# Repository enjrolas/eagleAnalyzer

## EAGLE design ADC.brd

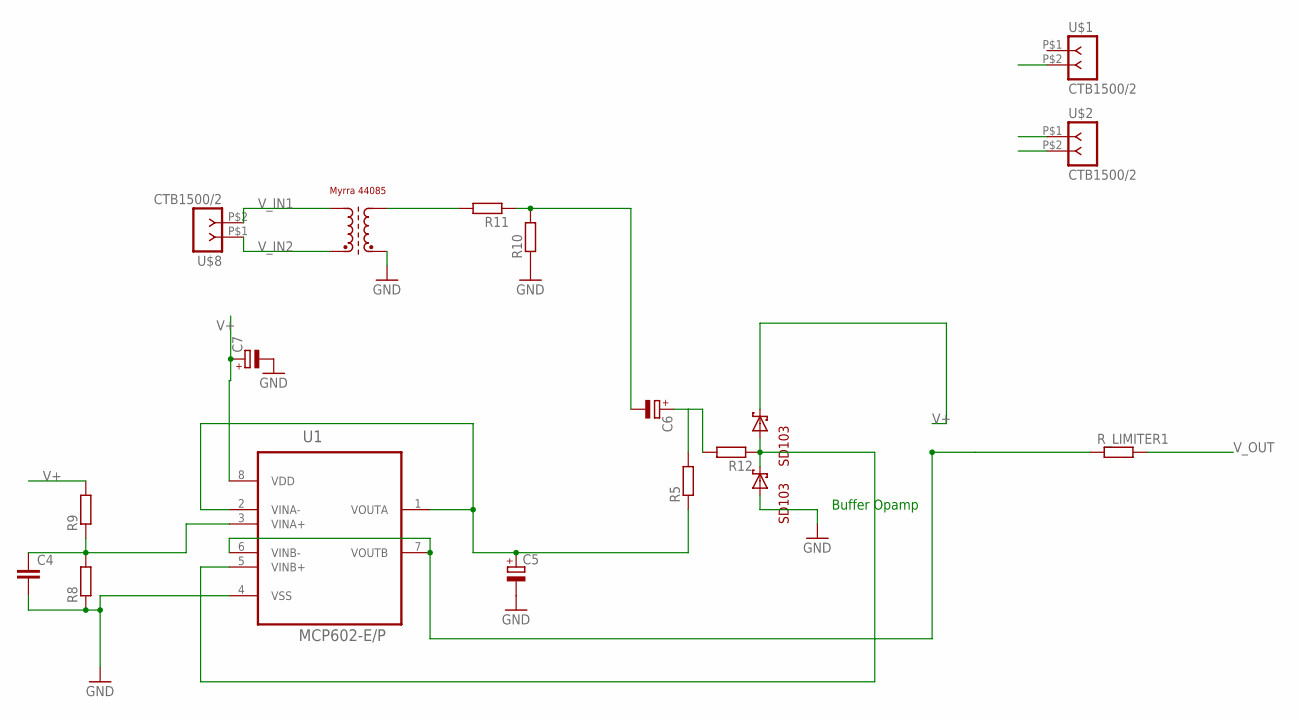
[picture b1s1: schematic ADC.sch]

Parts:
C4: C5P; C050-030-075
C5, C6, C7: CPOL1; E2,5-7---100UF
R5, R8, R9, R10, R11, R12: R; 0207/10
R_LIMITER1: R; 0207/10
U1: MCP602-E/P; DIP254P762X508-8P
U$1, U$2, U$8: CTB1500/2; CTB1500-2
U$5: MYRRA_4408; 4408
U$6, U$7: SD103A; D035-10

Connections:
GND: C4.2, C5.-, C7.-, R8.1, R10.1, U1.4 (VSS), U$2.P$1 (1), U$5.PIN9 (E2), U$7.A
unnamed: R_LIMITER1.1, U1.6 (VINB-), U1.7 (VOUTB)
unnamed: C5.+, R5.1, U1.1 (VOUTA), U1.2 (VINA-)
unnamed: C4.1, R8.2, R9.1, U1.3 (VINA+)
unnamed: R12.1, U1.5 (VINB+), U$6.A, U$7.C
unnamed: C6.-, R10.2, R11.1
unnamed: R11.2, U$5.PIN7 (A2)
unnamed: C6.+, R5.2, R12.2
V+: C7.+, R9.2, U1.8 (VDD), U$1.P$2 (2), U$6.C
V_IN1: U$5.PIN5 (A1), U$8.P$2 (2)
V_IN2: U$5.PIN1 (E1), U$8.P$1 (1)
V_OUT: R_LIMITER1.2, U$2.P$2 (2)

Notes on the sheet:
Buffer Opamp

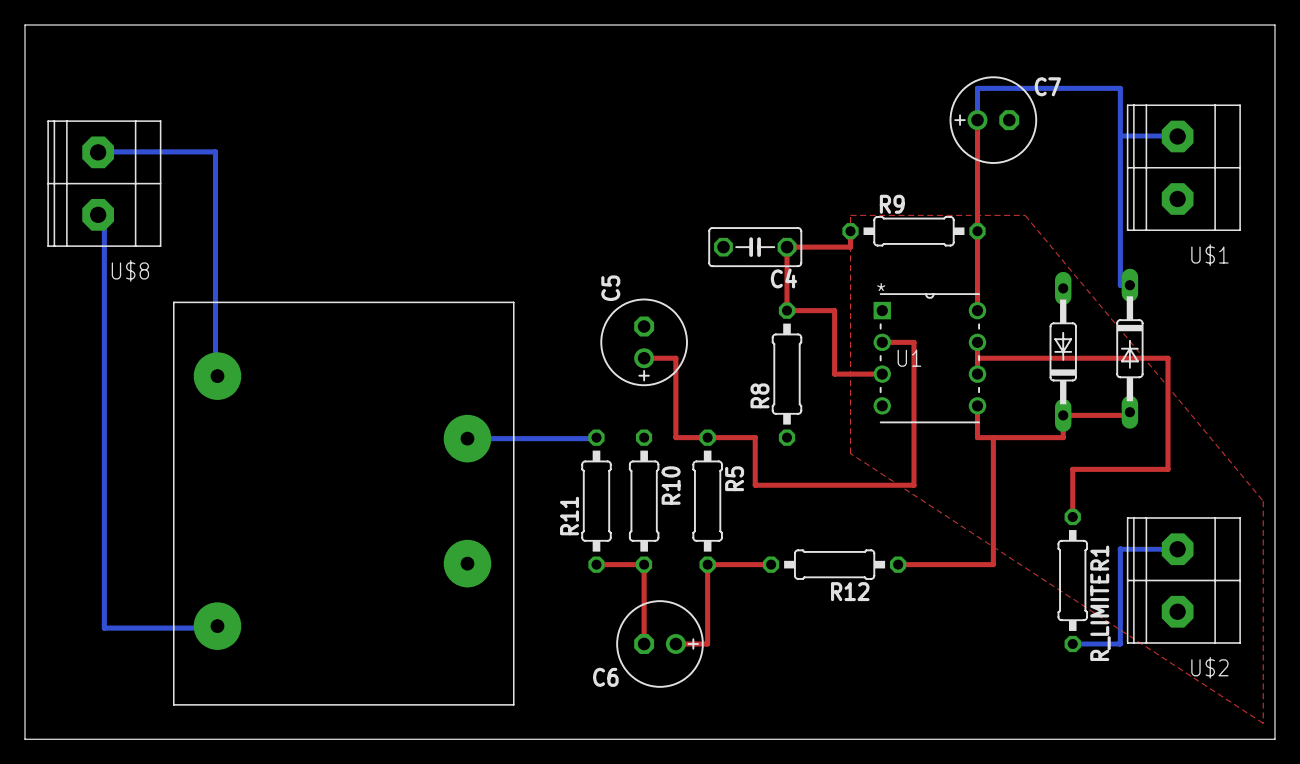
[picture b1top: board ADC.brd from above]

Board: 2 copper layers, 100.0 x 57.1 mm, 18 parts (0 on the bottom side), 12 nets.

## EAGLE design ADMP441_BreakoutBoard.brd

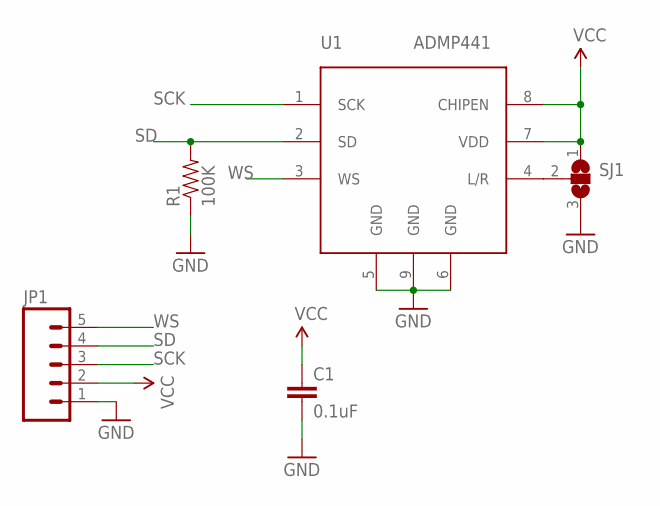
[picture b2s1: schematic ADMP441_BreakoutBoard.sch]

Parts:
C1: 0.1uF; 0603-CAP
JP1: M05PTH; 1X05
R1: 100K; 0603-RES
SJ1: SJ2W; SJ_2
U1: ADMP441

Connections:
GND: C1.2, JP1.1, R1.1, SJ1.3, U1.5 (GND), U1.6 (GND), U1.9 (GND)
unnamed: SJ1.2, U1.4 (L/R)
SCK: JP1.3, U1.1 (SCK)
SD: JP1.4, R1.2, U1.2 (SD)
VCC: C1.1, JP1.2, SJ1.1, U1.7 (VDD), U1.8 (CHIPEN)
WS: JP1.5, U1.3 (WS)

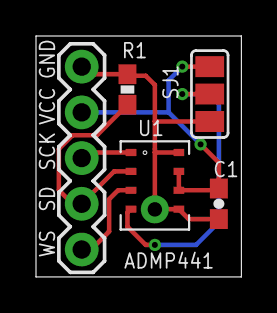
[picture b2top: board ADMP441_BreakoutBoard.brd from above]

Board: 2 copper layers, 11.4 x 13.4 mm, 5 parts (0 on the bottom side), 6 nets.

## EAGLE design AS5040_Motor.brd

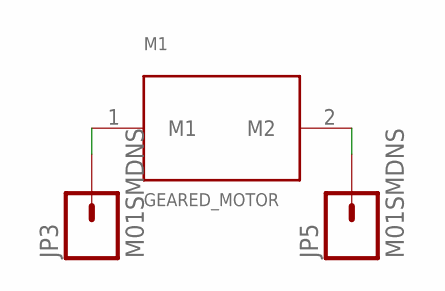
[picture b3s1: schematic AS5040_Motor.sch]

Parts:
JP3, JP5: M01SMDNS; 1X01NS
M1: GEARED_MOTOR

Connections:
unnamed: JP5.1, M1.2 (M2)
unnamed: JP3.1, M1.1 (M1)

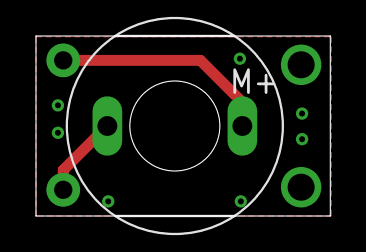
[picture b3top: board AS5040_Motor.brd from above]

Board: 2 copper layers, 16.4 x 10.0 mm, 3 parts (0 on the bottom side), 2 nets.

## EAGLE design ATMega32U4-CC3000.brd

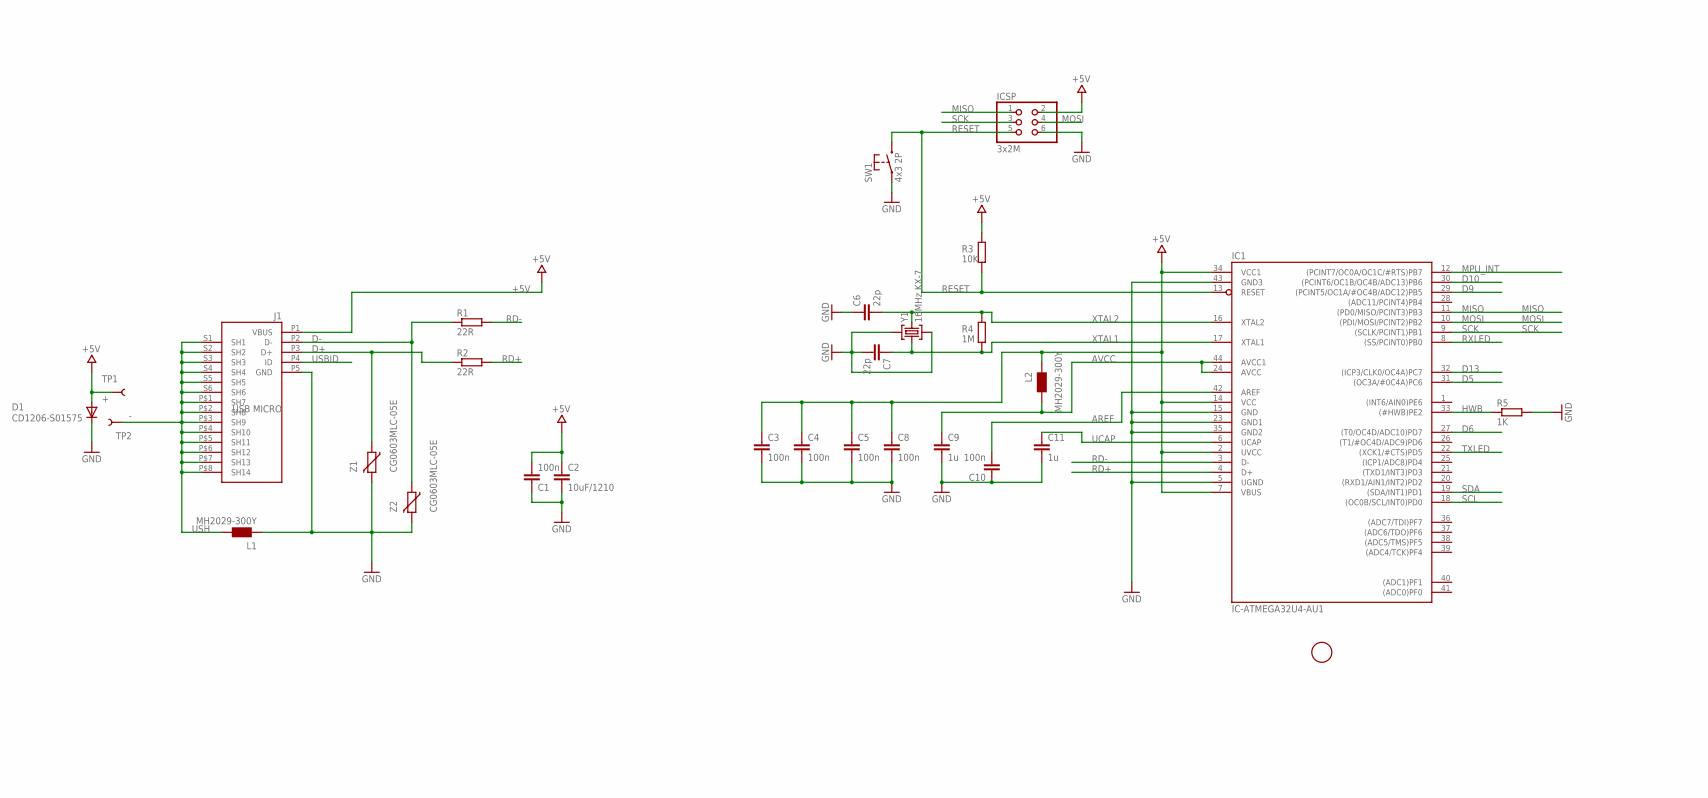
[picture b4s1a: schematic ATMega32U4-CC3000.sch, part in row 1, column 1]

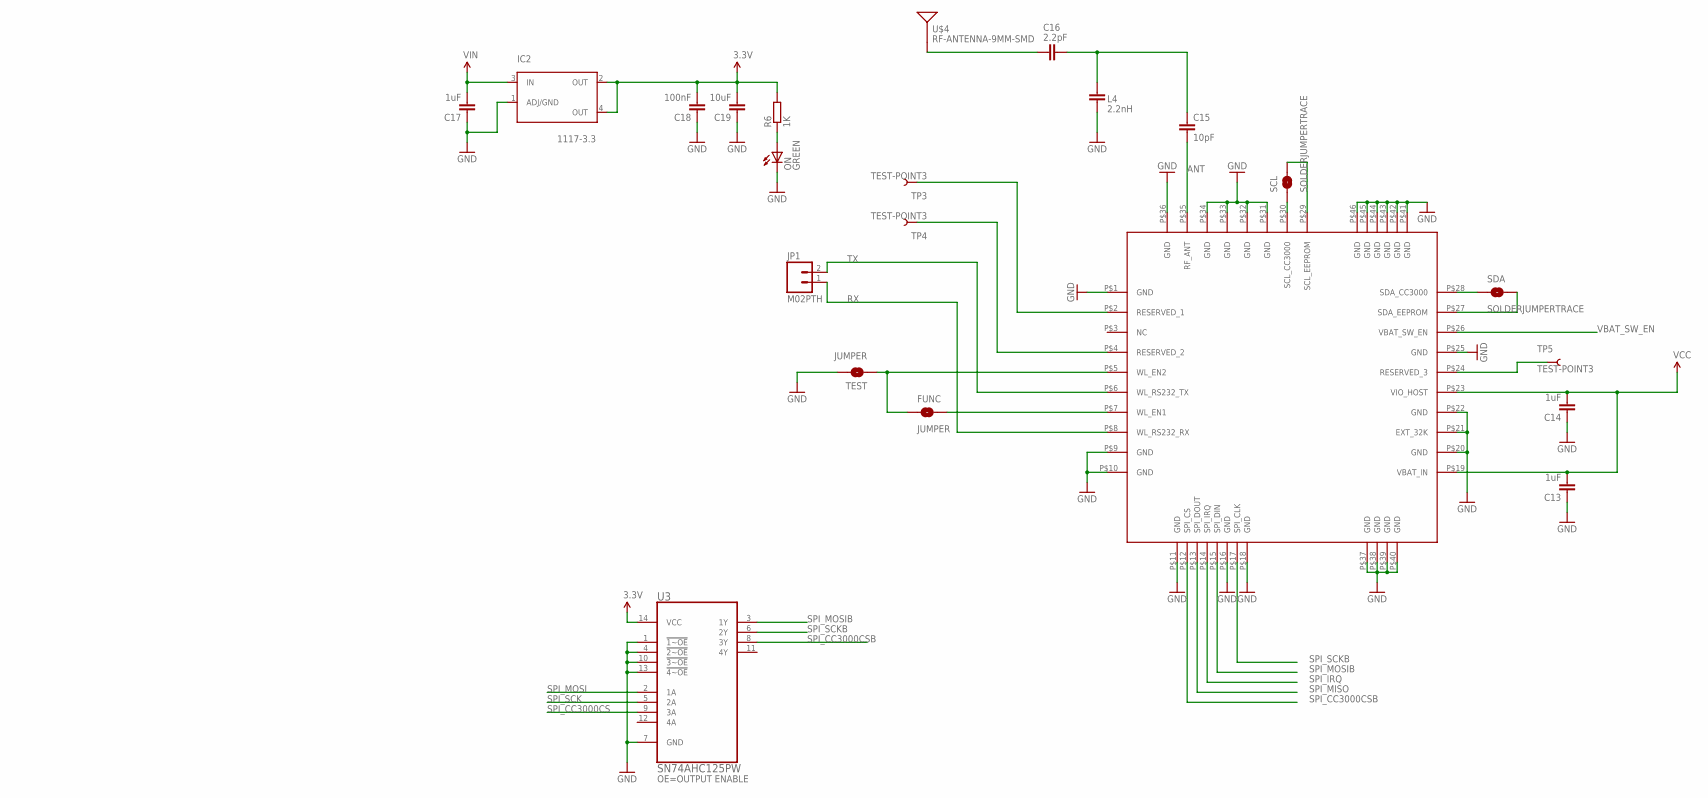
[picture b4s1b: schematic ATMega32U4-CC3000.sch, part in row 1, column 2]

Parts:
C1: 100n; C0603-ROUND
C2: 10uF/1210; CAP-1210_SMC-B-SMT
C3, C4, C5, C8, C10: 100n; CAP-0402-SMT-ROUND
C6, C7: 22p; CAP-0402-SMT-ROUND
C9, C11: 1u; CAP-0402-SMT-ROUND
C13, C14, C17: 1uF; CAP-0603-SMT-ROUND
C15: 10pF; CAP-0603-SMT-ROUND
C16: 2.2pF; CAP-0603-SMT-ROUND
C18: 100nF; CAP-0603-SMT-ROUND
C19: 10uF; CAP-1210_SMC-B-SMT
D1: CD1206-S01575; DIODE-1206-SMT
FID1: FIDUCIALMOUNT; FIDUCIA-MOUNT
FUNC: JUMPER; SJ_2S-TRACE
IC1: IC-ATMEGA32U4-AU1; QFP-10X10-44P
IC2: 1117-3.3; LDO-SOT223
ICSP: 3x2M; 2X03
J1: USB MICRO; CON2_USB_MICRO_B_AT
JP1: M02PTH; 1X02
L1, L2: MH2029-300Y; 0805
L4: 2.2nH; CAP-0603-SMT-ROUND
ON: GREEN; LED-0805-SMT
R1, R2: 22R; RESISTOR-0402-SMT-ROUND
R3: 10K; RESISTOR-0402-SMT-ROUND
R4: 1M; RESISTOR-0402-SMT-ROUND
R5: 1K; RESISTOR-0402-SMT-ROUND
R6: 1K; RESISTOR-0603-SMT-ROUND
SCL: SOLDERJUMPERTRACE; SJ_2S-TRACE
SDA: SOLDERJUMPERTRACE; SJ_2S-TRACE
SW1: 4x3 2P; SWITCH-2.1-SMT
TEST: JUMPER; SJ_2S-NO
TP1: +; PAD.03X.05
TP2: -; PAD.03X.05
TP3, TP4, TP5: TEST-POINT3; PAD.03X.03
U1: CC3000
U3: SN74AHC125PW; SOP65P640X120-14N
U$4: RF-ANTENNA-9MM-SMD; RF-ANTENNA-9MM
Y1: 16MHz KX-7; CRYSTAL-3.2-2.5
Z1, Z2: CG0603MLC-05E; CT/CN0603

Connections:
3.3V: C13.2, C14.2, C18.2, C19.- (2), IC2.2 (OUT), IC2.4 (OUT), R6.2, U1.P$19 (VBAT_IN), U1.P$23 (VIO_HOST), U3.14 (VCC)
+5V: C1.2, C2.+ (1), C3.1, C4.1, C5.1, C8.1, D1.A, IC1.2 (UVCC), IC1.7 (VBUS), IC1.14 (VCC), IC1.34 (VCC1), ICSP.2, J1.P1 (VBUS), L2.1, R3.1, TP1.P$1
ANT: C15.2, U1.P$35 (RF_ANT)
AREF: C10.2, IC1.42 (AREF)
AVCC: C9.1, IC1.24 (AVCC), IC1.44 (AVCC1), L2.2
D5: IC1.31 ((OC3A/#0C4A)PC6)
D6: IC1.27 ((T0/OC4D/ADC10)PD7)
D9: IC1.29 ((PCINT5/OC1A/#OC4B/ADC12)PB5)
D10: IC1.30 ((PCINT6/OC1B/OC4B/ADC13)PB6)
D13: IC1.32 ((ICP3/CLK0/OC4A)PC7)
D+: J1.P3 (D+), R2.1, Z1.1
D-: J1.P2 (D-), R1.1, Z2.1
GND: C1.1, C2.- (2), C3.2, C4.2, C5.2, C6.1, C7.2, C8.2, C9.2, C10.1, C11.2, C13.1, C14.1, C17.1, C18.1, C19.+ (1), D1.C, IC1.5 (UGND), IC1.15 (GND), IC1.23 (GND1), IC1.35 (GND2), IC1.43 (GND3), IC2.1 (ADJ/GND), ICSP.6, J1.P5 (GND), L1.1, L4.1, ON.C, R5.2, SW1.1, TEST.2, U1.P$1 (GND), U1.P$9 (GND), U1.P$10 (GND), U1.P$11 (GND), U1.P$16 (GND), U1.P$18 (GND), U1.P$20 (GND), U1.P$21 (EXT_32K), U1.P$22 (GND), U1.P$25 (GND), U1.P$31 (GND), U1.P$32 (GND), U1.P$33 (GND), U1.P$34 (GND), U1.P$36 (GND), U1.P$37 (GND), U1.P$38 (GND), U1.P$39 (GND), U1.P$40 (GND), U1.P$41 (GND), U1.P$42 (GND), U1.P$43 (GND), U1.P$44 (GND), U1.P$45 (GND), U1.P$46 (GND), U3.1 (!1~OE), U3.4 (!2~OE), U3.7 (GND), U3.10 (!3~OE), U3.13 (!4~OE), Y1.2 (GND), Y1.4 (GND), Z1.2, Z2.2
HWB: IC1.33 ((#HWB)PE2), R5.1
MISO: IC1.11 ((PD0/MISO/PCINT3)PB3), ICSP.1
MOSI: IC1.10 ((PDI/MOSI/PCINT2)PB2), ICSP.4
MPU_INT: IC1.12 ((PCINT7/OC0A/OC1C/#RTS)PB7)
unnamed: FUNC.2, U1.P$7 (WL_EN1)
unnamed: FUNC.1, TEST.1, U1.P$5 (WL_EN2)
unnamed: TP3.P$1, U1.P$2 (RESERVED_1)
unnamed: TP4.P$1, U1.P$4 (RESERVED_2)
unnamed: TP5.P$1, U1.P$24 (RESERVED_3)
unnamed: ON.A, R6.1
unnamed: C15.1, C16.2, L4.2
unnamed: SCL.1, U1.P$30 (SCL_CC3000)
unnamed: C16.1, U$4.SIG
unnamed: SCL.2, U1.P$29 (SCL_EEPROM)
unnamed: SDA.1, U1.P$28 (SDA_CC3000)
unnamed: SDA.2, U1.P$27 (SDA_EEPROM)
RD+: IC1.4 (D+), R2.2
RD-: IC1.3 (D-), R1.2
RESET: IC1.13 (RESET), ICSP.5, R3.2, SW1.2
RX: JP1.1, U1.P$8 (WL_RS232_RX)
RXLED: IC1.8 ((SS/PCINT0)PB0)
SCK: IC1.9 ((SCLK/PCINT1)PB1), ICSP.3
SCL: IC1.18 ((OC0B/SCL/INT0)PD0)
SDA: IC1.19 ((SDA/INT1)PD1)
SPI_CC3000CS: U3.9 (3A)
SPI_CC3000CSB: U1.P$12 (SPI_CS), U3.8 (3Y)
SPI_IRQ: U1.P$14 (SPI_IRQ)
SPI_MISO: U1.P$13 (SPI_DOUT)
SPI_MOSI: U3.2 (1A)
SPI_MOSIB: U1.P$15 (SPI_DIN), U3.3 (1Y)
SPI_SCK: U3.5 (2A)
SPI_SCKB: U1.P$17 (SPI_CLK), U3.6 (2Y)
TX: JP1.2, U1.P$6 (WL_RS232_TX)
TXLED: IC1.22 ((XCK1/#CTS)PD5)
UCAP: C11.1, IC1.6 (UCAP)
USBID: J1.P4 (ID)
USH: J1.P$1 (SH7), J1.P$2 (SH8), J1.P$3 (SH9), J1.P$4 (SH10), J1.P$5 (SH11), J1.P$6 (SH12), J1.P$7 (SH13), J1.P$8 (SH14), J1.S1 (SH1), J1.S2 (SH2), J1.S3 (SH3), J1.S4 (SH4), J1.S5 (SH5), J1.S6 (SH6), L1.2, TP2.P$1
VBAT_SW_EN: U1.P$26 (VBAT_SW_EN)
VIN: C17.2, IC2.3 (IN)
XTAL1: C7.1, IC1.17 (XTAL1), R4.1, Y1.1 (C1)
XTAL2: C6.2, IC1.16 (XTAL2), R4.2, Y1.3 (C2)

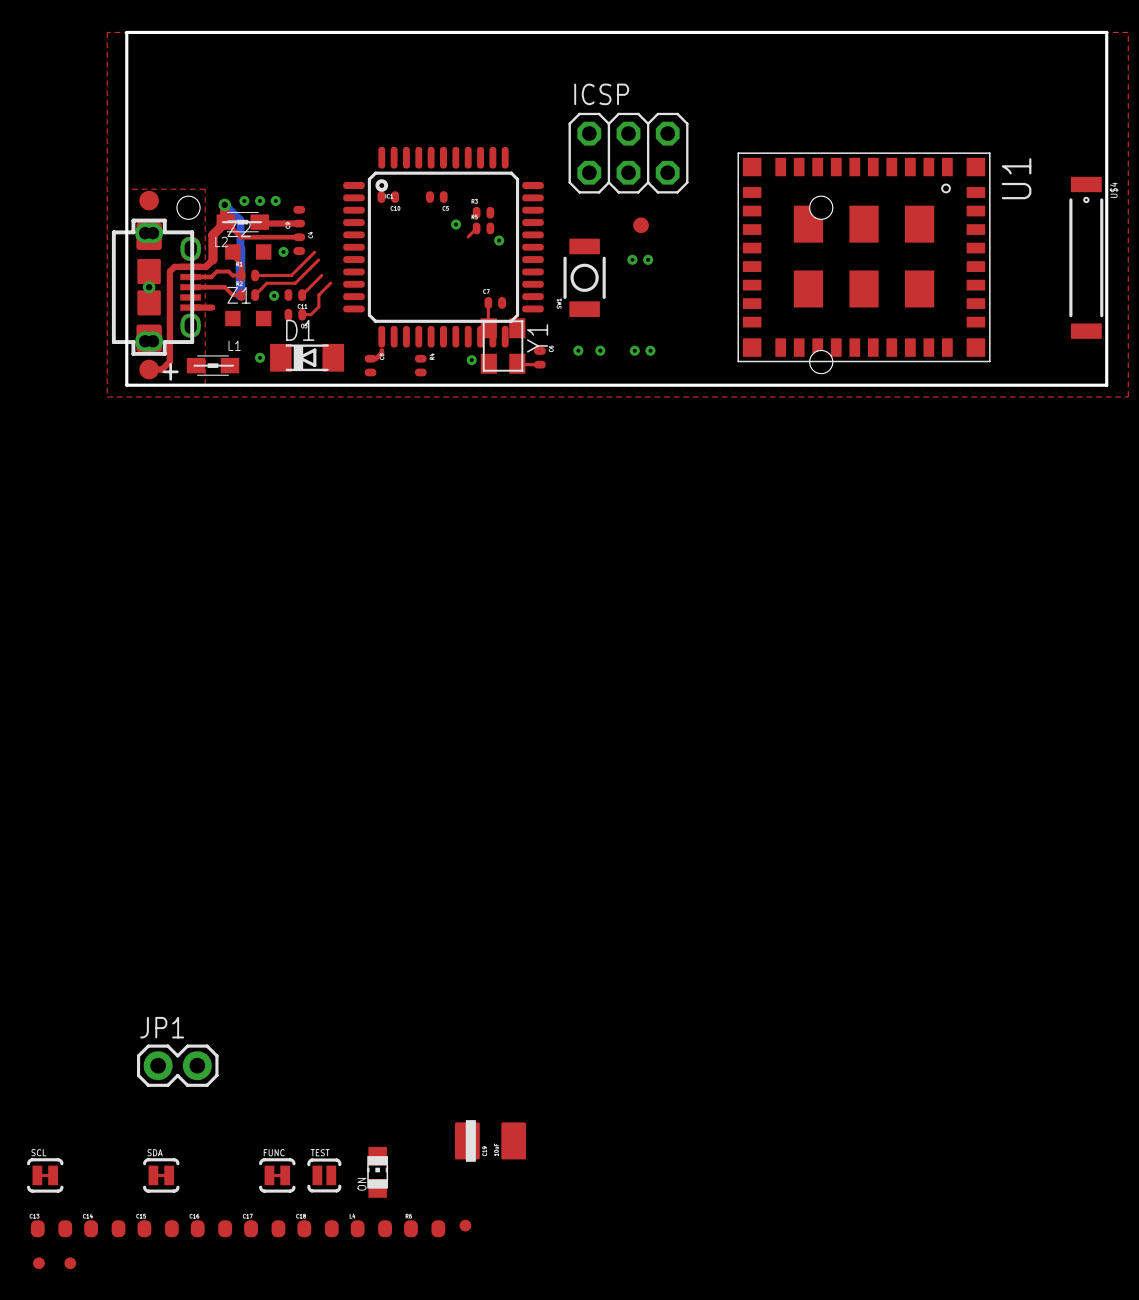
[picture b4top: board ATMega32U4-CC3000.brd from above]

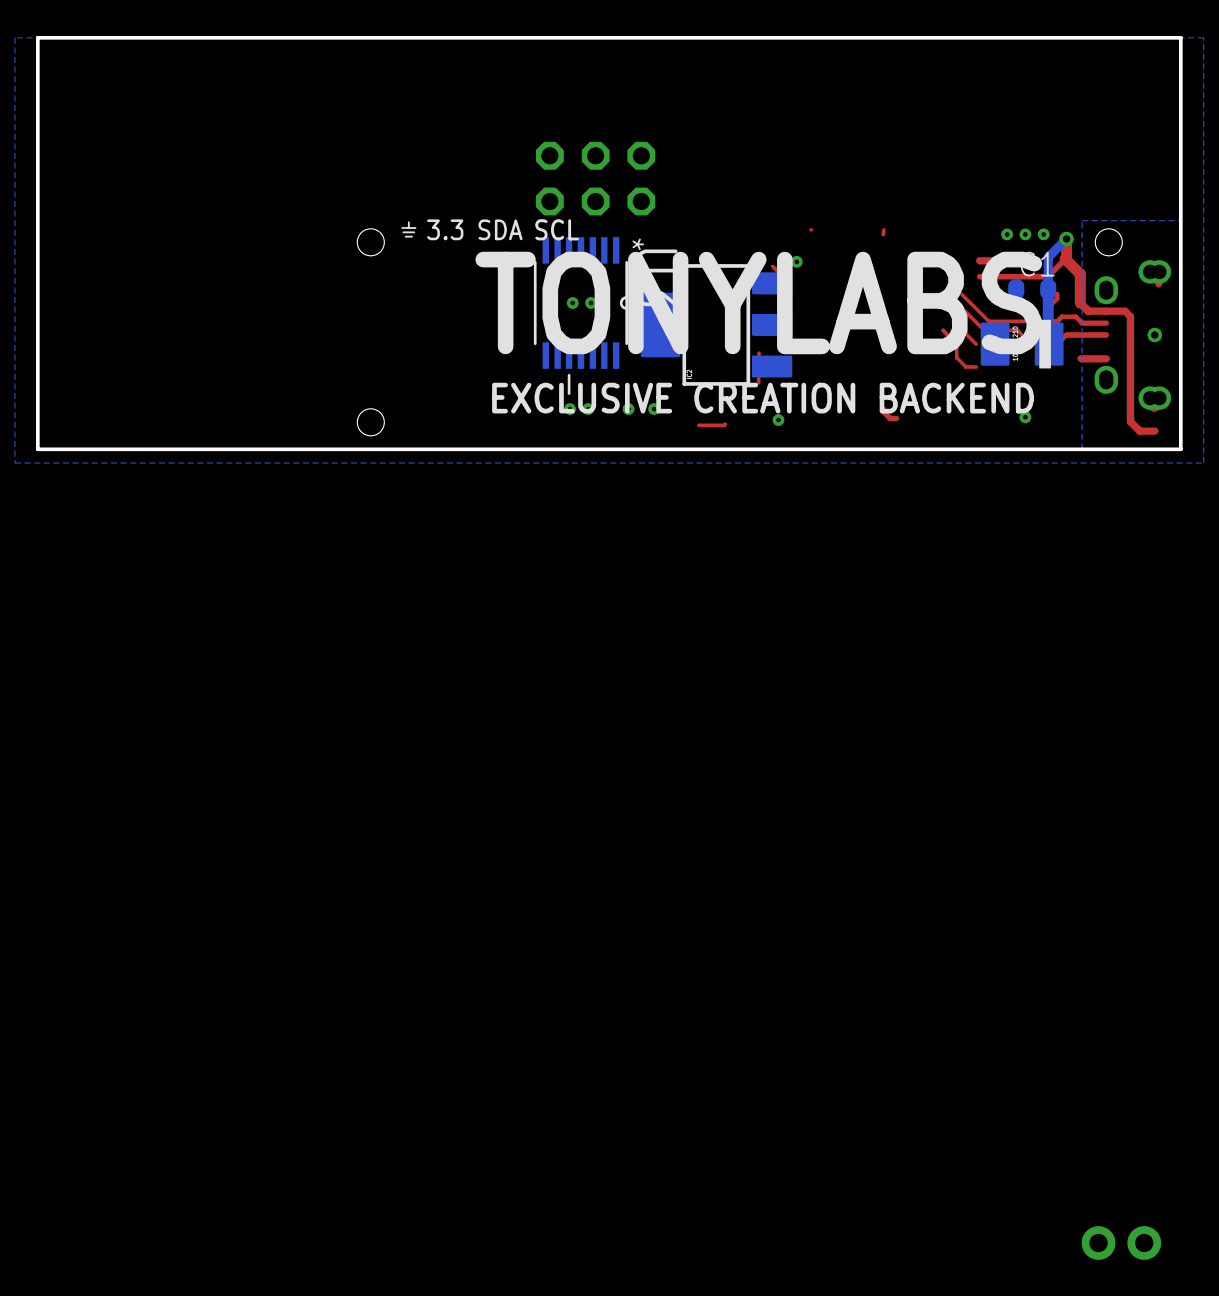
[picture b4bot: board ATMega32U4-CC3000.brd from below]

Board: 2 copper layers, 63.5 x 22.9 mm, 51 parts (4 on the bottom side), 37 nets.

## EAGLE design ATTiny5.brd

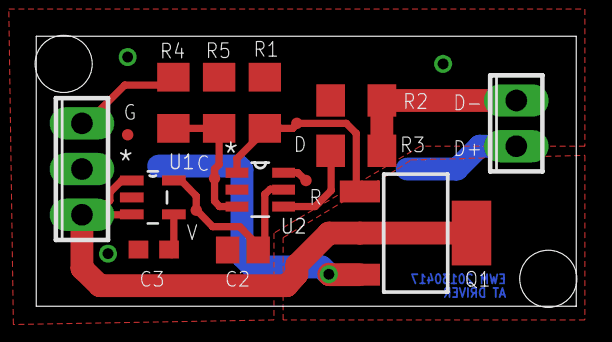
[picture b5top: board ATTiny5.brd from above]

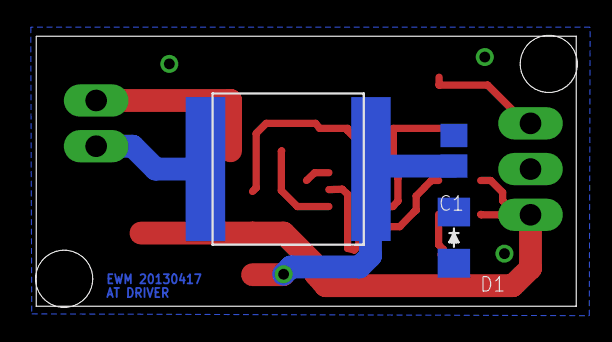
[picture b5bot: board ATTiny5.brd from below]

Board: 2 copper layers, 30.0 x 15.0 mm, 20 parts (3 on the bottom side), 12 nets.

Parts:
+5V: TPI; TPI_PAD
C1, C2: .1u; C0805
C3: 10n; C0603
D1: CD1206-B260; D1206
GND: TPI; TPI_PAD
L1: SRN8040
Q1: BSP100; SOT223
R1, R3: 10k; R1206
R2: 1; R1206
R4: 900; R1206
R5: 300; R1206
RESET: TPI; TPI_PAD
TPICLK: TPI; TPI_PAD
TPIDATA: TPI; TPI_PAD
U1: SPX5205M5-L-3-3; SOT95P280X145-5N
U2: ATTINY5-TSHR; SOT95P280X145-6N
X1: DIODES; 2POL254
X2: INPUT; 3POL254

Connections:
+14V: Q1.2, Q1.TAB, U1.1, U1.3, X2.1
BLINK: R4.1, R5.1, TPICLK.P$1, U2.3
D-: R2.2, R3.1, X1.2
GND: C1.2, C2.2, C3.2, D1.2, GND.P$1, R1.1, R2.1, R5.2, U1.2, U2.2, X2.2
L+: C1.1, D1.1, L1.P$1, Q1.3
MEASURE: R3.2, U2.4
MOSFET: Q1.1, R1.2, TPIDATA.P$1, U2.1
unnamed: R4.2, X2.3
unnamed: C3.1, U1.4
unnamed: L1.P$2, X1.1
RESET: RESET.P$1, U2.6
VCC: +5V.P$1, C2.1, U1.5, U2.5

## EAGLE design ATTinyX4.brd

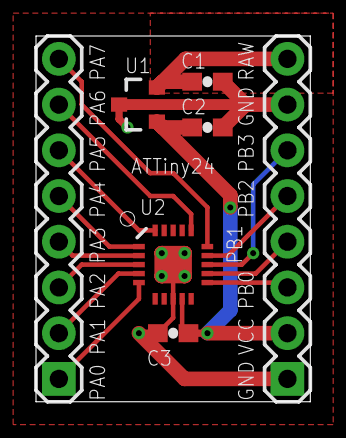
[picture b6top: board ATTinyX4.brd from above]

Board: 2 copper layers, 15.2 x 20.3 mm, 7 parts (0 on the bottom side), 15 nets.

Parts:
C1, C2, C3: 0.1uF; 0603-CAP
JP1: HEADER_A; 1X08
JP2: HEADER_B; 1X08
U1: LM3480IM4; SOT23-3
U2: ATTINY24QFN; QFN20

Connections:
GND: C1.2, C2.2, C3.1, JP2.1, JP2.7, U1.3, U2.0, U2.8
PA0: JP1.1, U2.5
PA1: JP1.2, U2.4
PA2: JP1.3, U2.3
PA3: JP1.4, U2.2
PA4: JP1.5, U2.1
PA5: JP1.6, U2.20
PA6: JP1.7, U2.16
PA7: JP1.8, U2.15
PB0: JP2.3, U2.11
PB1: JP2.4, U2.12
PB2: JP2.5, U2.14
PB3: JP2.6, U2.13
RAW: C1.1, JP2.8, U1.2
VCC: C2.1, C3.2, JP2.2, U1.1, U2.9

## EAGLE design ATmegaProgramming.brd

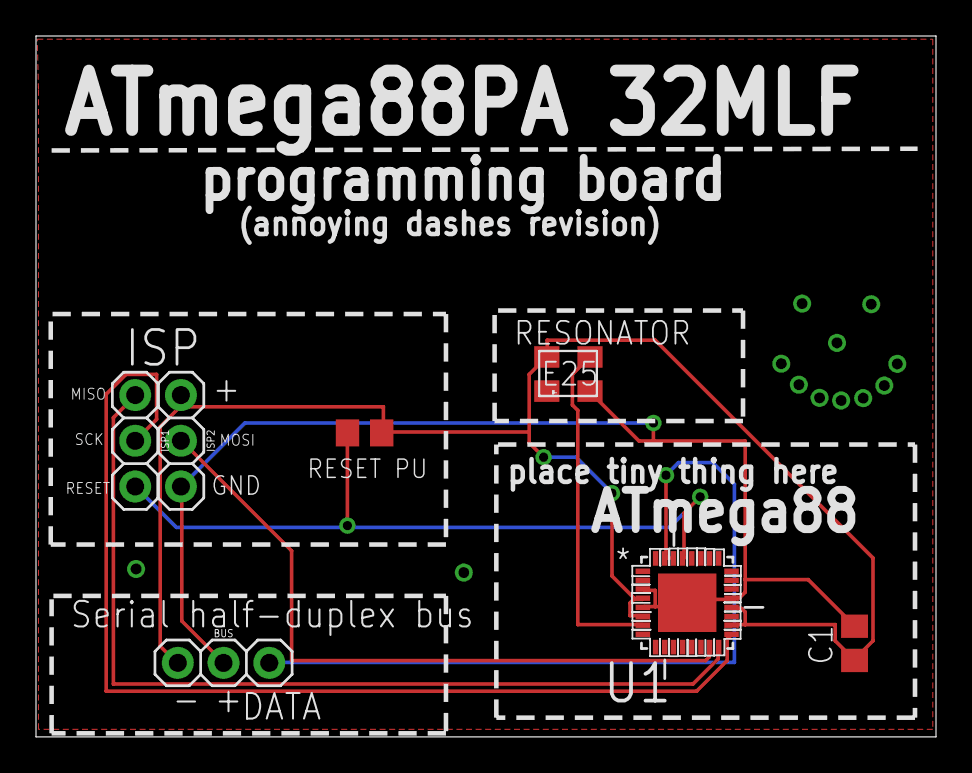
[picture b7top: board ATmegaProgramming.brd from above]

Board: 2 copper layers, 50.0 x 38.9 mm, 7 parts (0 on the bottom side), 8 nets.

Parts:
BUS: CONNEC_1X03
C1: 100nF; C0805
ISP1, ISP2: CONNEC_1X03
R1: R0805
RESONATOR: SG-310
U1: QFN50P500X500X100-33N

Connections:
CLOCK: RESONATOR.3, U1.7
DATA: BUS.3, U1.30, U1.31
GND: BUS.2, C1.2, ISP2.3, RESONATOR.2, U1.3, U1.5, U1.21, U1.33
MISO: ISP1.1, U1.16
MOSI: ISP2.2, U1.15
RESET: ISP1.3, R1.1, U1.29
SCK: ISP1.2, U1.17
VCC: BUS.1, C1.1, ISP2.1, R1.2, RESONATOR.4, U1.4, U1.6, U1.18, U1.20

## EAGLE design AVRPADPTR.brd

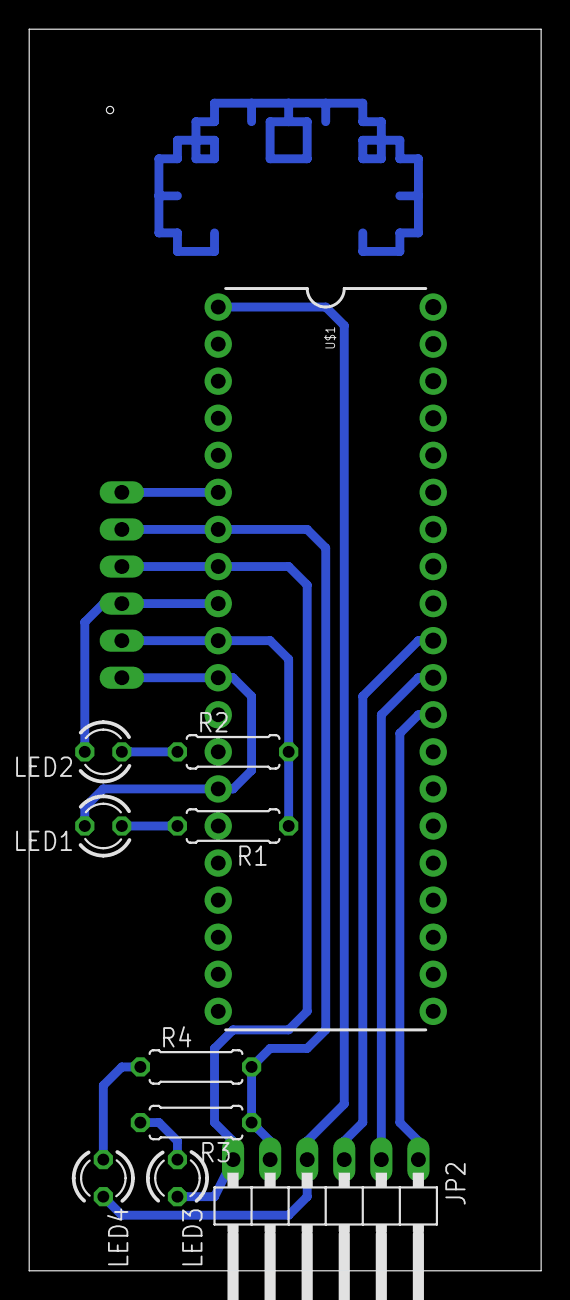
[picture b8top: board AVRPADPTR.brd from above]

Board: 2 copper layers, 35.1 x 85.1 mm, 11 parts (1 on the bottom side), 14 nets.

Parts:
JP1, JP2: 1X06/90
LED1, LED2, LED3, LED4: LED3MM
R1, R2, R3, R4: 0207/7
U$1: ZIFSOCKET-40-6DIL40-6-ZIF_SOCKET; DIL40-6-ZIF_SOCKET

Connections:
GND40: JP1.6, LED1.K, U$1.11
MISO28: JP2.2, U$1.30
MISO40_VCC28: JP1.2, JP2.5, R3.1, R4.2, U$1.7
MOSI28: JP2.1, U$1.29
MOSI40: JP1.1, U$1.6
unnamed: LED1.A, R1.2
unnamed: LED2.A, R2.1
unnamed: LED3.A, R3.2
unnamed: LED4.A, R4.1
RST28: JP2.4, LED4.K, U$1.1
RST40: JP1.4, LED2.K, U$1.9
SCK28: JP2.3, U$1.31
SCK40_GND28: JP1.3, JP2.6, LED3.K, U$1.8
VCC40: JP1.5, R1.1, R2.2, U$1.10

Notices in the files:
parts and their libraries:
SparkFun-Passives: Licensing: CC v3.0 Share-Alike You are welcome to use this library for commercial purposes.
